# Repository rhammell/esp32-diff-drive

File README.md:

# MDD32 Bot

A minimal two-wheeled differential-drive robot built around an ESP32-S3. The project includes the custom PCB, the 3D-printable chassis, and the firmware (packaged as an Arduino library).

The MDD32 board is a small, battery-powered controller for two-wheeled robots. It pairs an ESP32-S3 module with a dual H-bridge motor driver and connectors for two N20 gear motors with quadrature encoders. A single-cell Li-ion/LiPo battery powers the board, and it charges over USB-C. The same USB-C port is used for programming and serial debugging through the ESP32-S3's native USB.

## Repository Layout

| Folder | Description |
| --- | --- |
| [`firmware/`](firmware/) | ESP32 firmware, packaged as the `MDD32_Bot` Arduino library, plus example, test, and tuning sketches. |
| [`hardware/`](hardware/) | KiCad project for the PCB (schematic, board layout, and footprint/symbol/3D-model libraries). |
| [`mechanical/`](mechanical/) | FreeCAD source (`mechanical/src/`) and exported STLs (`mechanical/export/`) for the chassis. |
| [`images/`](images/) | README images. |

## Board Features

- **ESP32-S3-MINI-1-N8** module with Wi-Fi and Bluetooth LE
- **Native USB-C** for programming, serial, and charging; no USB-UART bridge needed
- **Single-cell Li-ion/LiPo charging** with power-path management (TI BQ24072)
- **5 V boost converter** for the motor supply (TI TPS61023)
- **3.3 V LDO** for the logic supply (Diodes AP2114H-3.3)
- **Dual H-bridge motor driver** with per-channel current limiting (TI DRV8833)
- **Two 6-pin JST-SH motor ports** for N20 encoder motors
- **Battery voltage sensing** that only draws current while the board is switched on
- **Charge and USB-power status**, shown on LEDs and readable by the ESP32
- **Slide power switch**, plus RESET and BOOT buttons
- **4-layer, 62 × 28 mm PCB** with four M2.5 mounting holes

## Hardware

### Power

| Rail       | Source                       | Feeds                          |
|------------|------------------------------|--------------------------------|
| `VBUS`     | USB-C (5 V)                  | Battery charger input          |
| `VBAT`     | 1S Li-ion/LiPo via JST-PH 2-pin | Charger battery pin         |
| `VSYS`     | Charger power-path output, through the power switch | LDO and boost converter |
| `+3V3`     | AP2114H-3.3 LDO              | ESP32-S3 and encoders          |
| `+5V`      | TPS61023 boost (≈4.96 V)     | DRV8833 motor supply           |

- **Charger:** the BQ24072's input current limit is set to about 1.4 A (R9 = 1.1 kΩ) and its fast-charge current to about 330 mA (R10 = 2.7 kΩ). Size your battery for this charge rate, or change R10.
- **Motor current limit:** each DRV8833 channel limits at about 0.67 A (300 mΩ sense resistors).

### ESP32-S3 Pin Map

| GPIO   | Signal       | Function                              |
|--------|--------------|---------------------------------------|
| IO0    | `BOOT`       | BOOT button (strapping pin)           |
| EN     | `RESET`      | RESET button                          |
| IO10   | `VBAT_MON`   | Battery voltage, ½ divider (ADC)      |
| IO35   | `PGOOD_MON`  | USB power present (active low)        |
| IO36   | `CHG_MON`    | Charging (active low)                 |
| IO40   | `SLEEP`      | DRV8833 nSLEEP (high = enabled)       |
| IO47   | `MOT1_IN1`   | Left motor driver input 1 (AIN1)      |
| IO33   | `MOT1_IN2`   | Left motor driver input 2 (AIN2)      |
| IO38   | `MOT1_ENCA`  | Left encoder channel A                |
| IO39   | `MOT1_ENCB`  | Left encoder channel B                |
| IO48   | `MOT2_IN1`   | Right motor driver input 1 (BIN1)     |
| IO34   | `MOT2_IN2`   | Right motor driver input 2 (BIN2)     |
| IO41   | `MOT2_ENCA`  | Right encoder channel A               |
| IO42   | `MOT2_ENCB`  | Right encoder channel B               |
| IO19/20| `USB_D-`/`USB_D+` | Native USB                       |

### Connectors

| Ref | Connector            | Pinout                                              |
|-----|----------------------|-----------------------------------------------------|
| J1  | JST-PH 2-pin         | 1: `VBAT`, 2: `GND`                                 |
| J2  | USB-C (USB 2.0)      | Power and data                                      |
| J4  | JST-SH 6-pin (MOT L) | 1: `GND`, 2: `ENC_B`, 3: `ENC_A`, 4: `3V3`, 5: `M2`, 6: `M1` |
| J5  | JST-SH 6-pin (MOT R) | 1: `GND`, 2: `ENC_B`, 3: `ENC_A`, 4: `3V3`, 5: `M2`, 6: `M1` |

### Opening the PCB

1. Open `hardware/MDD32_Bot/MDD32_Bot.kicad_pro` in **KiCad 10** or newer.
2. The project's symbol, footprint, and 3D model libraries are referenced relative to the project folder, so no extra library setup is needed.
3. Each component in the schematic has an LCSC part number in its `LCSC` field for JLCPCB assembly. The [Fabrication Toolkit](https://github.com/bennymeg/Fabrication-Toolkit) plugin can generate the Gerbers, BOM, and placement file in one step.

## Firmware

The firmware lives in `firmware/MDD32_Bot/`, structured as an Arduino library with no external dependencies:

| Path | Description |
| --- | --- |
| `src/MDD32_Bot.h` / `.cpp` | Top-level `MDD32_Bot` class that ties the subsystems together. |
| `src/definitions/` | Compile-time configuration: `pin_definitions.h` (wiring) and `robot_definitions.h` (tuning/behavior). |
| `src/battery/` | `MDD32_Battery`: battery voltage and charger-status monitoring. |
| `src/drive/` | Differential drive stack: `MDD32_Motor`, `MDD32_Encoder`, `MDD32_PID`, `MDD32_Motor_Controller`, and `MDD32_Drive`. |
| `examples/` | Standalone feature demos: `BatteryTest`, `WifiTest`. |
| `tuning/` | Calibration sketches, numbered in the order they should be run: `1_FeedforwardTuning`, `2_PIDTuning`, `3_WheelSyncTuning`, `4_DistanceTuning`. |
| `tests/` | Post-build verification sketches: `ForwardTest`, `DriftTest`, `DriveCycleTest`. |

All sketches report over the Serial Monitor at 115200 baud.

### Installing

Copy or symlink `firmware/MDD32_Bot` into your Arduino `libraries` folder (for example `~/Documents/Arduino/libraries/MDD32_Bot`), and install the **esp32 by Espressif Systems** board package.

### Board settings

In the Arduino IDE, select **ESP32S3 Dev Module** and set:

- **USB CDC On Boot:** Enabled (required for Serial output over the native USB port)
- **Flash Size:** 8MB
- **PSRAM:** Disabled

The ESP32-S3 is programmed over USB-C. If the port doesn't appear, hold **BOOT**, press and release **RESET**, then release **BOOT** to enter the bootloader.

### Usage

```cpp
#include <MDD32_Bot.h>

MDD32_Bot bot;

void setup() {
    Serial.begin(115200);
    if (!bot.begin()) {
        Serial.println("MDD32 Bot init failed");
        while (1);
    }
    bot.drive.straight(6.0f);   // drive forward at 6 cm/s
}

void loop() {
    bot.drive.update();         // must be called frequently for PID control
}
```

`MDD32_Bot` exposes two subsystems: `battery` (`voltage()`, `charging()`, `chargerConnected()`) and `drive` (`straight()`, `spin()`, `stop()`, `update()`, `isMoving()`, `getTelemetry()`, `getDistance()`, `resetDistance()`).

## License

This project is licensed under the [MIT License](LICENSE).

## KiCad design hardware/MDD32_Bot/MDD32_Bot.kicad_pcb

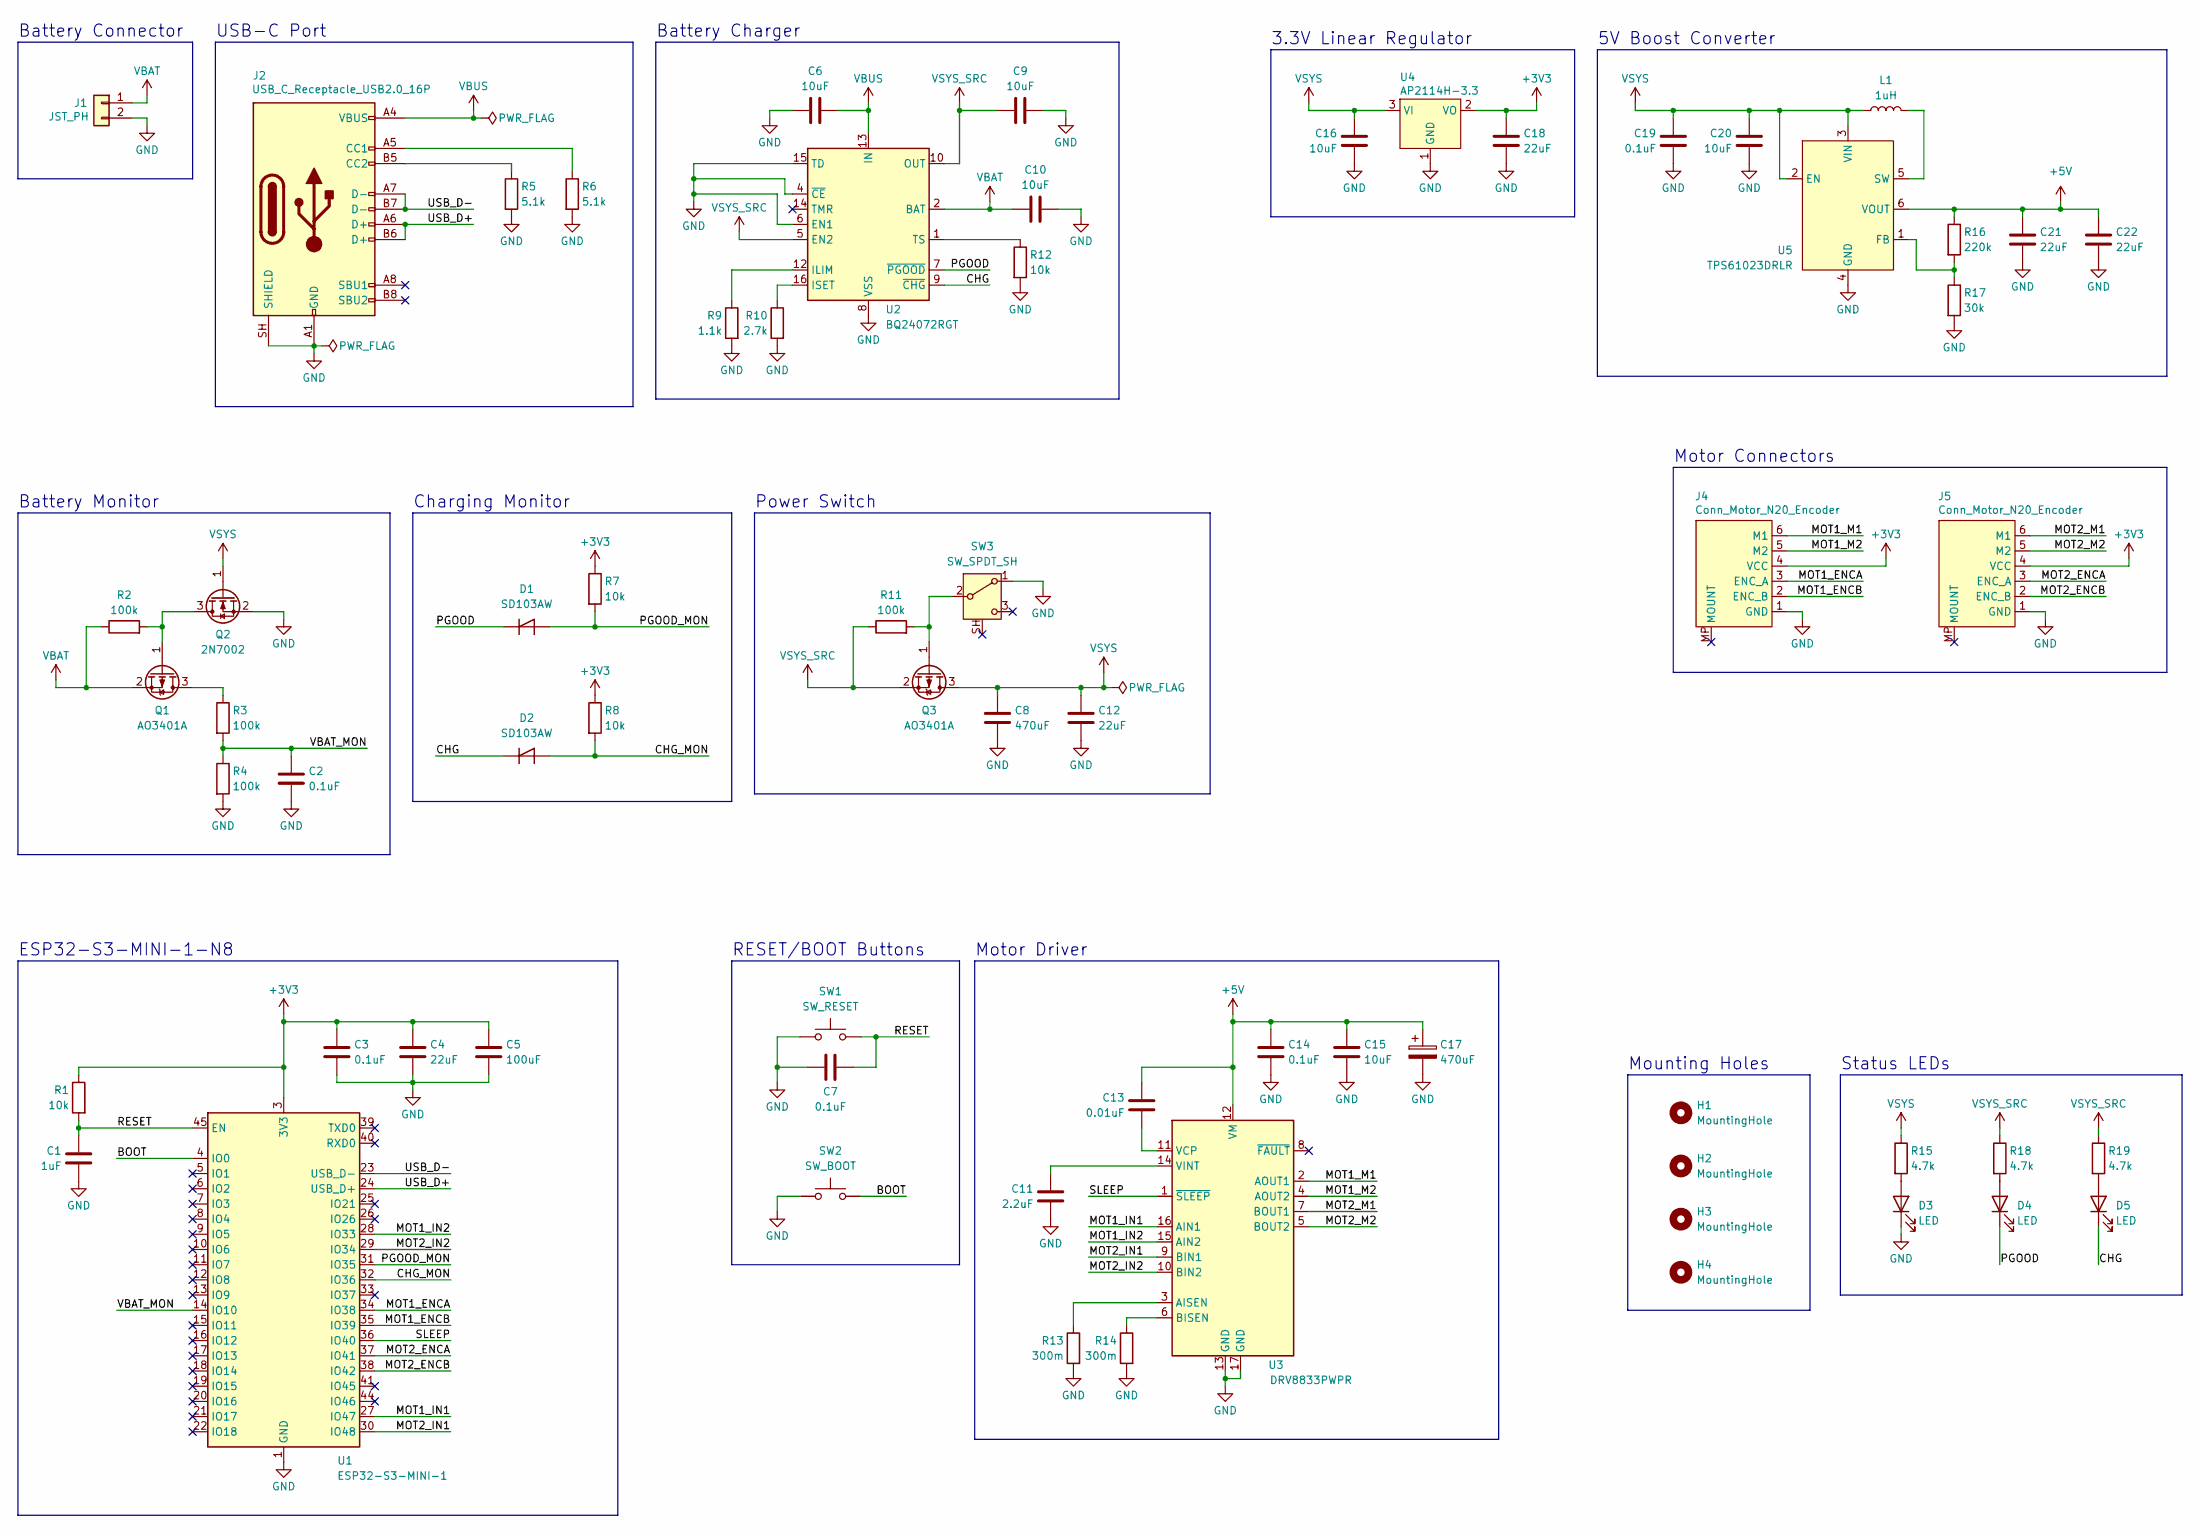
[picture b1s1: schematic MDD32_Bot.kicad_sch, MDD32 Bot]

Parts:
C1: 1uF; C_0603_1608Metric; LCSC C15849
C2, C3, C7, C14, C19: 0.1uF; C_0603_1608Metric; LCSC C14663
C4, C12, C18, C21, C22: 22uF; C_0805_2012Metric; LCSC C45783
C5: 100uF; C_1206_3216Metric; LCSC C15008
C6, C9, C10, C15, C16, C20: 10uF; C_0805_2012Metric; LCSC C15850
C8, C17: 470uF; CP_Elec_6.3x7.7; LCSC C344072
C11: 2.2uF; C_0603_1608Metric; LCSC C23630
C13: 0.01uF; C_0603_1608Metric; LCSC C57112
D1, D2: SD103AW; D_SOD-123; LCSC C7502706
D3: LED; LED_0805_2012Metric; LCSC C2297
D4, D5: LED; LED_0805_2012Metric; LCSC C2296
H1, H2, H3, H4: MountingHole; MountingHole_2.7mm_M2.5
J1: JST_PH; JST_PH_B2B-PH-K_1x02_P2.00mm_Vertical; LCSC C131337
J2: USB_C_Receptacle_USB2.0_16P; USB_C_Receptacle_G-Switch_GT-USB-7010ASV; LCSC C2988369
J4, J5: Conn_Motor_N20_Encoder; JST_SH_BM06B-SRSS-TB_1x06-1MP_P1.00mm_Vertical; LCSC C495540
L1: 1uH; L_Coilcraft_XxL4030; LCSC C5441341
Q1, Q3: AO3401A; SOT-23; LCSC C15127
Q2: 2N7002; SOT-23; LCSC C8545
R1, R7, R8, R12: 10k; R_0603_1608Metric; LCSC C25804
R2, R3, R4, R11: 100k; R_0603_1608Metric; LCSC C25803
R5, R6: 5.1k; R_0603_1608Metric; LCSC C23186
R9: 1.1k; R_0603_1608Metric; LCSC C22764
R10: 2.7k; R_0603_1608Metric; LCSC C13167
R13, R14: 300m; R_1206_3216Metric; LCSC C22464904
R15, R18, R19: 4.7k; R_0603_1608Metric; LCSC C23162
R16: 220k; R_0603_1608Metric; LCSC C22961
R17: 30k; R_0603_1608Metric; LCSC C22984
SW1: SW_RESET; SW_SPST_TS-1088-xR020; LCSC C720477
SW2: SW_BOOT; SW_SPST_TS-1088-xR020; LCSC C720477
SW3: SW_SPDT_SH; SW_SPDT_Shouhan_MSK12C02; LCSC C431541
U1: ESP32-S3-MINI-1; LCSC C2913206
U2: BQ24072RGT; VQFN-16-1EP_3x3mm_P0.5mm_EP1.6x1.6mm_ThermalVias; LCSC C140288
U3: DRV8833PWPR; HTSSOP-16-1EP_4.4x5mm_P0.65mm_EP3.4x5mm_Mask2.66x2.46mm_The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; LCSC C50506
U4: AP2114H-3.3; SOT-223-3_TabPin2; LCSC C150716
U5: TPS61023DRLR; SOT-563; LCSC C919459

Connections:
+3V3: C3.1, C4.1, C5.1, C18.1, J4.4 (VCC), J5.4 (VCC), R1.1, R7.1, R8.1, U1.3 (3V3), U4.2 (VO)
+5V: C13.1, C14.1, C15.1, C17.1, C21.1, C22.1, R16.1, U3.12 (VM), U5.6 (VOUT)
/BOOT: SW2.2, U1.4 (IO0)
/CHG: D2.1 (K), D5.1 (K), U2.9 (~CHG)
/CHG_MON: D2.2 (A), R8.2, U1.32 (IO36)
/CS: U1.21 (IO17)
/DC: U1.19 (IO15)
/LITE: U1.16 (IO12)
/MOSI: U1.18 (IO14)
/MOT1_ENCA: J4.3 (ENC_A), U1.34 (IO38)
/MOT1_ENCB: J4.2 (ENC_B), U1.35 (IO39)
/MOT1_IN1: U1.27 (IO47), U3.16 (AIN1)
/MOT1_IN2: U1.28 (IO33), U3.15 (AIN2)
/MOT1_M1: J4.6 (M1), U3.2 (AOUT1)
/MOT1_M2: J4.5 (M2), U3.4 (AOUT2)
/MOT2_ENCA: J5.3 (ENC_A), U1.37 (IO41)
/MOT2_ENCB: J5.2 (ENC_B), U1.38 (IO42)
/MOT2_IN1: U1.30 (IO48), U3.9 (BIN1)
/MOT2_IN2: U1.29 (IO34), U3.10 (BIN2)
/MOT2_M1: J5.6 (M1), U3.7 (BOUT1)
/MOT2_M2: J5.5 (M2), U3.5 (BOUT2)
/PGOOD: D1.1 (K), D4.1 (K), U2.7 (~PGOOD)
/PGOOD_MON: D1.2 (A), R7.2, U1.31 (IO35)
/RESET: C1.1, C7.1, R1.2, SW1.2, U1.45 (EN)
/RST: U1.20 (IO16)
/SCK: U1.17 (IO13)
/SCL: U1.22 (IO18)
/SDA: U1.25 (IO21)
/SLEEP: U1.36 (IO40), U3.1 (~SLEEP)
/USB_D+: J2.A6 (D+), J2.B6 (D+), U1.24 (USB_D+)
/USB_D-: J2.A7 (D-), J2.B7 (D-), U1.23 (USB_D-)
/VBAT_MON: C2.1, R3.2, R4.1, U1.14 (IO10)
GND: C1.2, C2.2, C3.2, C4.2, C5.2, C6.1, C7.2, C8.2, C9.2, C10.2, C11.2, C12.2, C14.2, C15.2, C16.2, C17.2, C18.2, C19.2, C20.2, C21.2, C22.2, D3.1 (K), J1.2, J2.A1 (GND), J2.A12 (GND), J2.B1 (GND), J2.B12 (GND), J2.S1 (SHIELD), J2.SH (SHIELD), J4.1 (GND), J5.1 (GND), Q2.2 (S), R4.2, R5.2, R6.2, R9.2, R10.2, R12.2, R13.2, R14.2, R17.2, SW1.1, SW2.1, SW3.1 (A), U1.1 (GND), U1.2 (GND), U1.42 (GND), U1.43 (GND), U1.46 (GND), U1.47 (GND), U1.48 (GND), U1.49 (GND), U1.50 (GND), U1.51 (GND), U1.52 (GND), U1.53 (GND), U1.54 (GND), U1.55 (GND), U1.56 (GND), U1.57 (GND), U1.58 (GND), U1.59 (GND), U1.60 (GND), U1.61 (GND), U1.62 (GND), U1.63 (GND), U1.64 (GND), U1.65 (GND), U2.4 (~CE), U2.6 (EN1), U2.8 (VSS), U2.15 (TD), U2.17 (VSS), U3.13 (GND), U3.17 (GND), U4.1 (GND), U5.4 (GND)
unnamed: D3.2 (A), R15.2
unnamed: D4.2 (A), R18.2
unnamed: D5.2 (A), R19.2
unnamed: J2.A5 (CC1), R6.1
unnamed: J2.B5 (CC2), R5.1
unnamed: Q1.3 (D), R3.1
unnamed: Q1.1 (G), Q2.3 (D), R2.2
unnamed: Q3.1 (G), R11.2, SW3.2 (B)
unnamed: R9.1, U2.12 (ILIM)
unnamed: R10.1, U2.16 (ISET)
unnamed: R12.1, U2.1 (TS)
unnamed: R13.1, U3.3 (AISEN)
unnamed: R14.1, U3.6 (BISEN)
unnamed: C13.2, U3.11 (VCP)
unnamed: C11.1, U3.14 (VINT)
unnamed: R16.2, R17.1, U5.1 (FB)
unnamed: L1.2, U5.5 (SW)
VBAT: C10.1, J1.1, Q1.2 (S), R2.1, U2.2 (BAT), U2.3 (BAT)
VBUS: C6.2, J2.A4 (VBUS), J2.A9 (VBUS), J2.B4 (VBUS), J2.B9 (VBUS), U2.13 (IN)
VSYS: C8.1, C12.1, C16.1, C19.1, C20.1, L1.1, Q2.1 (G), Q3.3 (D), R15.1, U4.3 (VI), U5.2 (EN), U5.3 (VIN)
VSYS_SRC: C9.1, Q3.2 (S), R11.1, R18.1, R19.1, U2.5 (EN2), U2.10 (OUT), U2.11 (OUT)

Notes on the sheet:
Motor Connectors
ESP32-S3-MINI-1-N8
RESET/BOOT Buttons
Battery Charger
Battery Monitor
Charging Monitor
5V Boost Converter
Status LEDs
3.3V Linear Regulator
Mounting Holes
USB-C Port
Battery Connector
Power Switch
Motor Driver

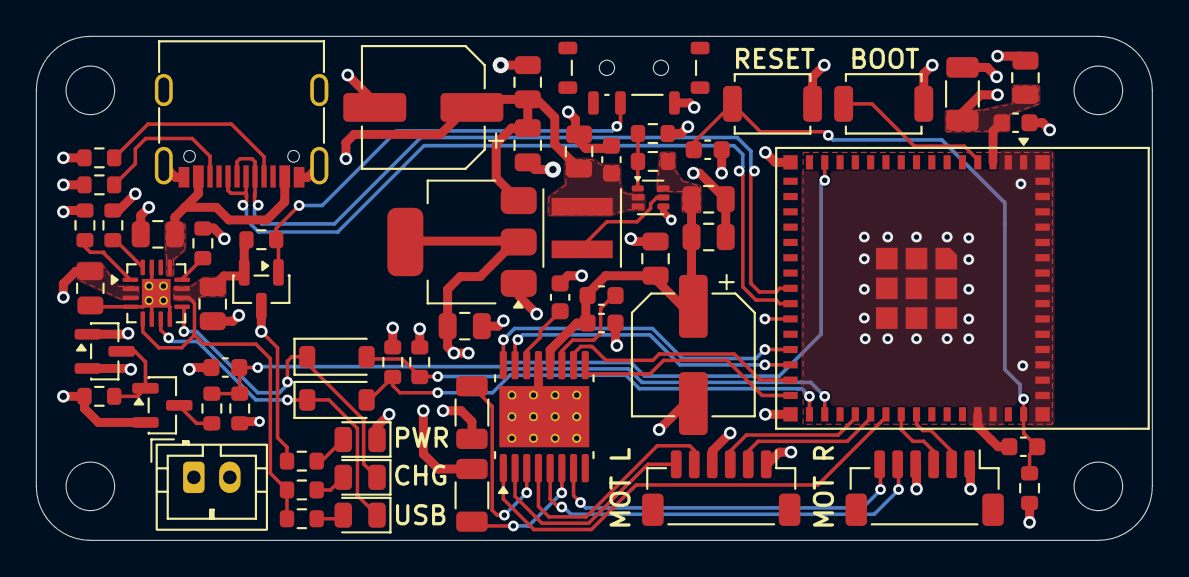
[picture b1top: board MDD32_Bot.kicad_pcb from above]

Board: 4 copper layers, 62.0 x 28.0 mm, 66 parts (0 on the bottom side), 46 nets.
